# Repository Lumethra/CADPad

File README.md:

# CADPad

## What is this?? 

SHHH, this is a gift, dont spoiler it, SHHHH. But what exactly is this?? Good question. Its a keyboard. Again. Wait, what does again mean, well its my second one. My [Auth75](https://github.com/Lumethra/Auth75) was my first one. Back to what this is. Its technically a keyboard, but I would rather call it a Macropad, because its firmwares purpose is to make 3d modeling in Onshape easier. This is also why its called a CADPad, not Catpad (meow), CADPad. C A D, like CAD-design. 

### Features: 
  - custom 27 keys leyout
      - its kinda ergonomic? kinda.
  - Nice!Nano V2
      - ZMK firmware (hand written, yeeeeee)
      - better ZMK support, because Nice!Nano V2
      - build in BLE support
      - LiPo battery support
      - battery charger + support
  - USB Hub (SL2.1)
      - 1 USB-C upsream
      - 4 USB-C donwstreams
      - USB 2.0 fullspeed

---

## Why though?

This is a gift to [Chroma](https://github.com/Chroma165), my friend who likes to design 3d-models and print them with his 3d-printer. I though it would be nice to gift him a Macropad, my bad, its a CADPad, to make this process easier for him. It was also fun to design a PCB, that has a unique form. 

---

## How?

This CADPads development process was fairly easiy because of the knowledge from Auth75. It has 3 layers of keybinds, which u can cycle through with pressing the 2nd knob. The other knobs keypress is reserved for BLE pairing. 

---

## Renders

| PCB with Components |
| --- |
|  |
|  |

| PCB without Components |
| --- |
|  |
|  |

| Case |
| --- |
|  |

---

## PCB + Schematics

| PCB |
| --- |
|  |

| Schematics |
| --- |
|  |

---

<details>
  <summary>
    <h2>Zine</h2> 
  </summary>

| Zine |
| --- |
|  |

---
</details>

## BOM

| Part | Purpose | Cost | Quantity | Total Cost | LCSC/JLCPC Number | Link |
| --- | --- | --- | --- | --- | --- | --- |
| PCB | connect all of the compoenents | $14.10 | 1 (5) | $14.10 | ~ | [JLCPCB](https://jlcpcb.com/) |
| Nice!Nano V2 | handle the firmware | €24.63 | 1 | €24.63 | ~ | [42keebs](https://42keebs.eu/shop/parts/controllers/nice-nano-v2-wireless-controller/) | 
| Kailh Hotswap Sockets | holding the switches to the PCB without soldering | $0.1183 | 78 | ~$9 | C2803348 | [JLCPCB](https://jlcpcb.com/partdetail/C2803348) |
| Kailh (Cocoa) Switches | the switches you can press | $0 (comes with a Rainy75) | 78 | $0 (already owned) | ~ | ~ |
| Keycaps | goes onto the switches for better look and feel | $0 (3d printing ABS) | 78 | $0 (3d printed) | ~ | ~ |
| EC11 Rotary Encoder Switch | goes uii and click click | $2.22 | 1 | $2.22 | C370970 | [JLCPCB](https://jlcpcb.com/partdetail/C370970) / [Amazon](https://www.amazon.de/-/en/RUNCCI-YUN-Potentiometer-Automotive-Electronics-Multimedia/dp/B09SG3HF9N) |
| USB-C connector | connect to laptop | $0.0740 | 4 | $0.296 | C2765186 | [JLCPCB](https://jlcpcb.com/partdetail/C2765186) |
| SL2.1s | USB Hub core component | $0.2258 | 1 | $0.2258 | C2684433 | [JLCPCB](https://jlcpcb.com/partdetail/C2684433) |
| DW01A | battery protector | $0.0426 | 1 | $0.0426 | C351410 | [JLCPCB](https://jlcpcb.com/partdetail/C351410) |
| FS8205A | mosfet for protector | $0.0470 | 1 | $0.0470 | C2830320 | [JLCPCB](https://jlcpcb.com/partdetail/C2830320) |
| S2B-PH-SM4-TB | LiPo battery connector | $0.2014 | 1 | $0.2014 | C295747 | [JLCPCB](https://jlcpcb.com/partdetail/C295747) |
| Diodes | prevent voltage from backflowing and causing problems | $0.0117 | 82 | ~$0.9594 | C81598 | [JLCPCB](https://jlcpcb.com/partdetail/C81598) |
| Resistors | prevent things go boom | ~$0.0016 | 19 | ~$0.0304 | C23186, C21190, C22775 | [C23186](https://jlcpcb.com/partdetail/C23186) / [C21190](https://jlcpcb.com/partdetail/C21190) / [C22775](https://jlcpcb.com/partdetail/C22775) |
| Capacitors | smooth out the power | $0.0032 - $0.0110 | 14 | ~$0.0956 | C15849, C19666, C14663 | [C15849](https://jlcpcb.com/partdetail/C15849) / [C19666](https://jlcpcb.com/partdetail/C19666) / [C14663](https://jlcpcb.com/partdetail/C14663) |

> the prices can vary depending on the provider <br>
> you can find the JLCPCB parts on [LCSC](https://lcsc.com/) too (exept the PCB and the Pico)

--- 

## Contribute

Want to make anything better? Found any bugs? Anything always going booom?? Feel free to open a PR (pull request) and lets make the project better. ^_^
> the libraries are all imported with [easyeda2kicad](https://github.com/uPesy/easyeda2kicad.py) and [kiswitch](https://github.com/kiswitch/kiswitch)

---

## Thank you

A huge thank you too all these persons helping me making this project possible, thank you helping me sanity check, thank you for all these support. 
> Thank you, <3 u all ^_^

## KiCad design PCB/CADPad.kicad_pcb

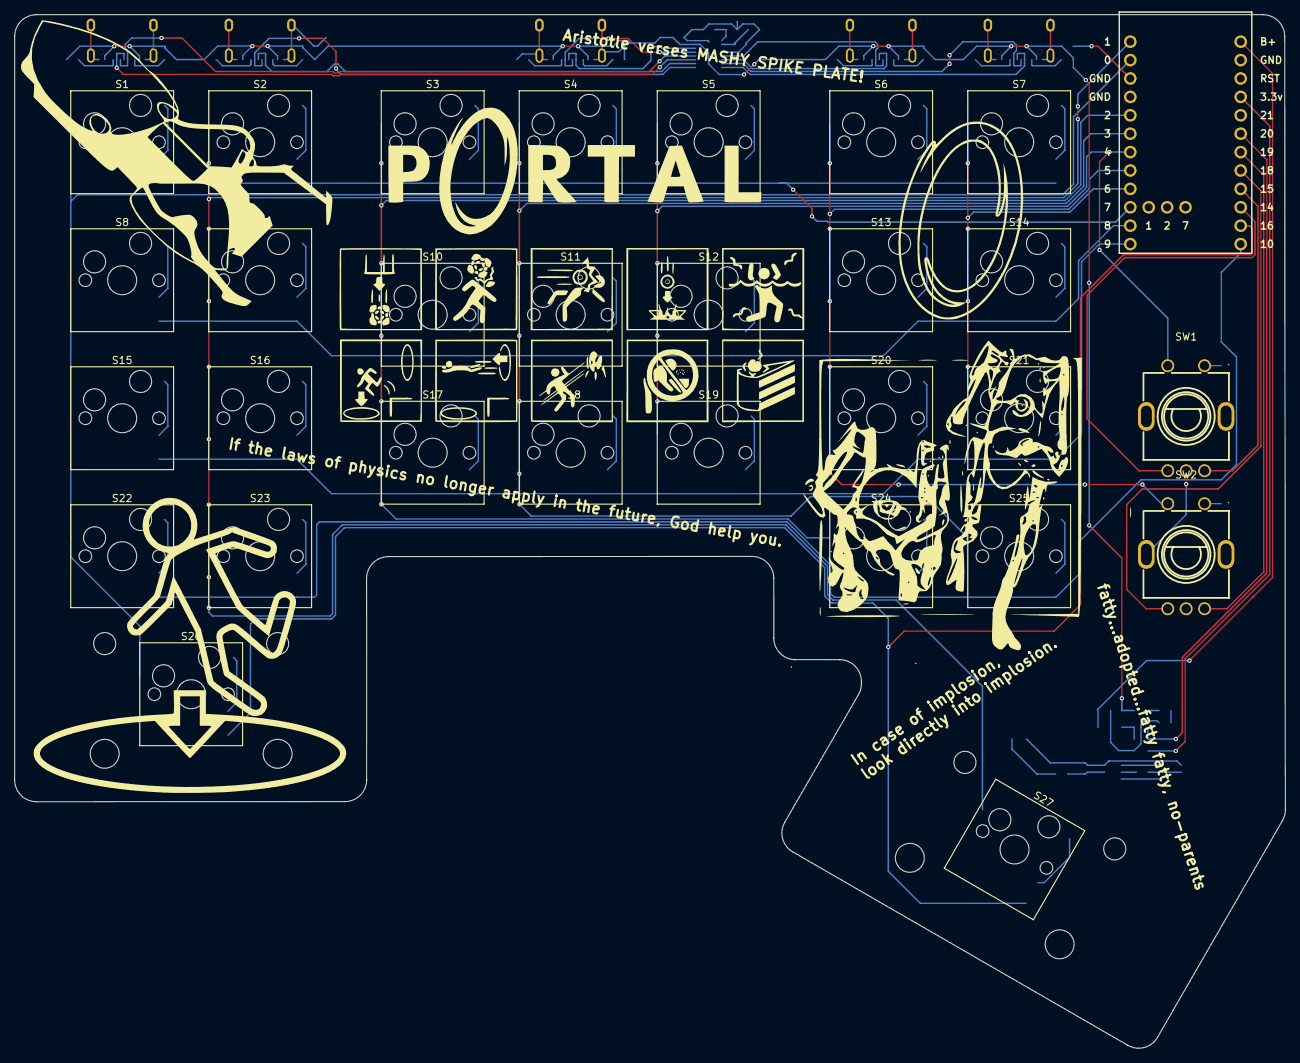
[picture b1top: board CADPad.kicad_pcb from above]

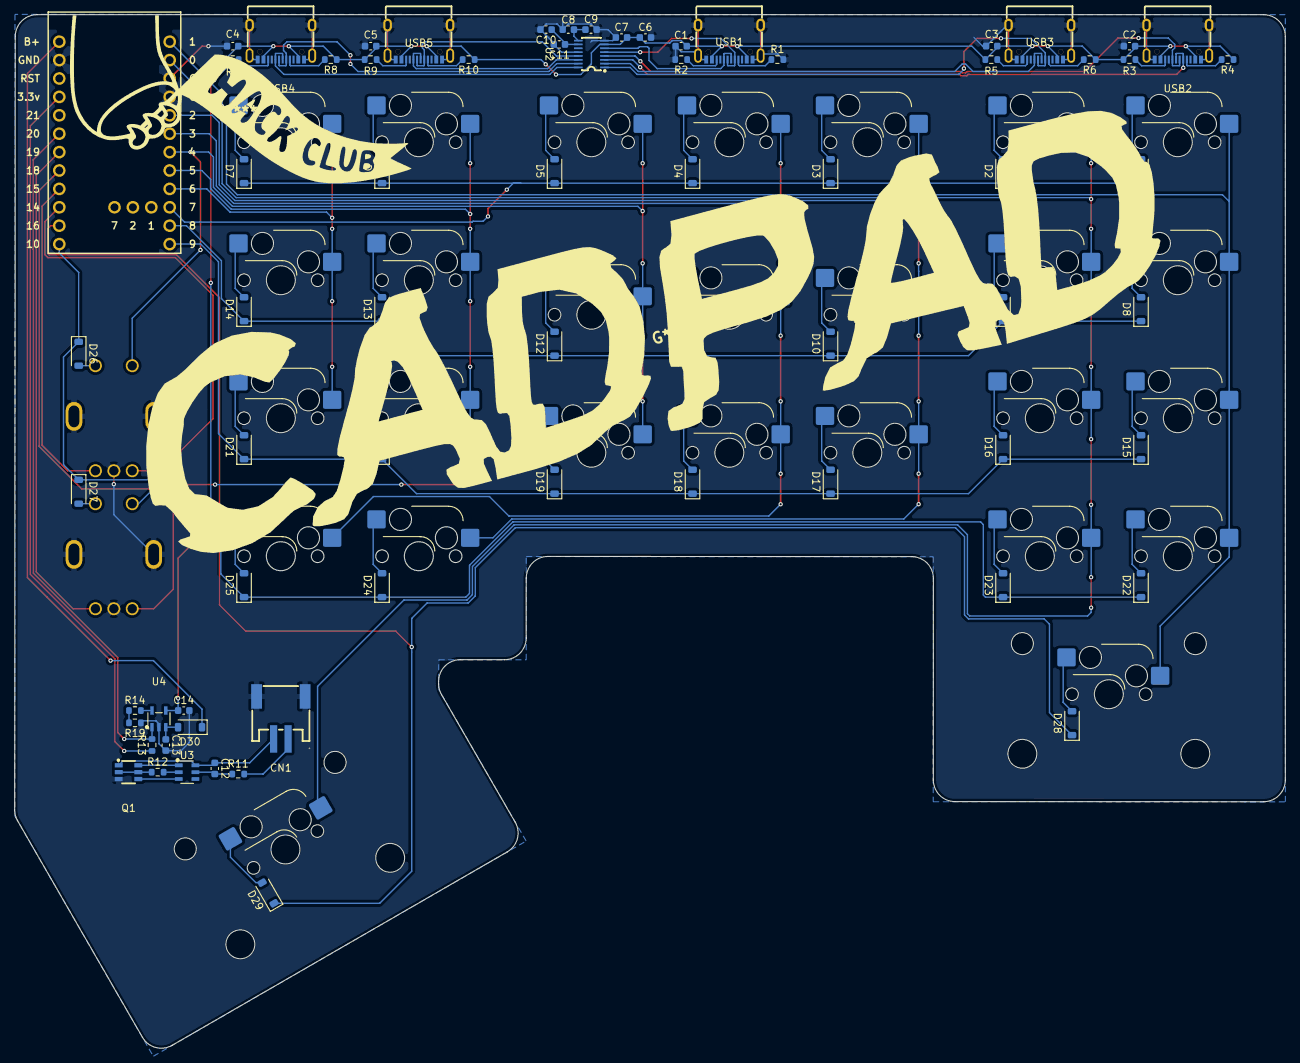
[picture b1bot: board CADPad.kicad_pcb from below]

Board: 2 copper layers, 175.4 x 142.7 mm, 99 parts (69 on the bottom side), 82 nets.

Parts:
C1, C2, C3, C4, C5, C6, C8, C10: 1uf; C_0603_1608Metric
C7, C9, C11, C12: 100nf; C_0603_1608Metric
C13, C14: 4.7uF; C_0603_1608Metric
CN1: S2B-PH-SM4-TB; CONN-SMD_P2.00_S2B-PH-SM4-TB-LF-SN
D1, D2, D3, D4, D5, D6, D7, D8, D9, D10, D11, D12, D13, D14, D15, D16, D17, D18, D19, D20, D21, D22, D23, D24, D25, D26, D27, D28, D29, D30: D_SOD-123
Q1: FS8205A_C2830320; SOT-23-6_L2.9-W1.6-P0.95-LS2.8-BR
R1, R2, R3, R4, R5, R6, R7, R8, R9, R10, R13: 5.1k; R_0603_1608Metric
R11: 100; R_0603_1608Metric
R12, R14, R19: 1k; R_0603_1608Metric
S1, S2, S3, S4, S5, S6, S7, S8, S9, S10, S11, S12, S13, S14, S15, S16, S17, S18, S19, S20, S21, S22, S23, S24, S25, S26, S27: SW_Hotswap_Kailh_MX
SW1, SW2: EC11E15244G1; SW-TH_EC11E15244G1
U1: Nice_Nano_V2
U2: SL2.1S; SSOP-16_L4.6-W2.6-P0.53-LS4.0-BL
U3: DW01A_C351410; SOT-23-6_L2.9-W1.6-P0.95-LS2.8-BL
U4: MCP73831T-2ACI/OT; SOT-23-5_L3.0-W1.7-P0.95-LS2.8-BL
USB1, USB2, USB3, USB4, USB5: TYPE-C 16PIN 2MD; USB-C-SMD_TYPE-C-6PIN-2MD-073

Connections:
+3.3V: R13.1, U1.21 (3.3v)
+5V: C1.1, C2.1, C3.1, C4.1, C5.1, C6.1, C7.1, C14.1, R3.1, R4.1, R5.1, R6.1, R7.1, R8.1, R9.1, R10.1, U2.7 (VDD5), U4.4 (VDD), USB1.2 (VBUS), USB1.11 (VBUS), USB2.2 (VBUS), USB2.11 (VBUS), USB3.2 (VBUS), USB3.11 (VBUS), USB4.2 (VBUS), USB4.11 (VBUS), USB5.2 (VBUS), USB5.11 (VBUS)
/D1/D2: Q1.2 (D1/D2), Q1.5 (D1/D2), R12.1
/DN: U2.5 (UDM), USB1.5 (DN2), USB1.7 (DN1)
/DN1: U2.3 (DM1), USB2.5 (DN2), USB2.7 (DN1)
/DN2: U2.1 (DM2), USB3.5 (DN2), USB3.7 (DN1)
/DN3: U2.15 (DM3), USB4.5 (DN2), USB4.7 (DN1)
/DN4: U2.13 (DM4), USB5.5 (DN2), USB5.7 (DN1)
/DP: U2.6 (UDP), USB1.6 (DP1), USB1.8 (DP2)
/DP1: U2.4 (DP1), USB2.6 (DP1), USB2.8 (DP2)
/DP2: U2.2 (DP2), USB3.6 (DP1), USB3.8 (DP2)
/DP3: U2.16 (DP3), USB4.6 (DP1), USB4.8 (DP2)
/DP4: U2.14 (DP4), USB5.6 (DP1), USB5.8 (DP2)
BATT+: C13.1, D30.2 (A), U4.3 (VBAT)
Batt+: CN1.1, R11.2
Batt-: C12.1, CN1.2, Q1.1 (S1), U3.6 (GND)
Column 1: S1.1, S8.1, S15.1, S22.1, S26.1, U1.2 (0)
Column 2: S2.1, S9.1, S16.1, S23.1, S27.1, U1.1
Column 3: S3.1, S10.1, S17.1, S24.1, U1.5 (2)
Column 4: S4.1, S11.1, S18.1, S25.1, U1.6 (3)
Column 5: S5.1, S12.1, S19.1, SW1.D, U1.7 (4)
Column 6: S6.1, S13.1, S20.1, SW2.D, U1.8 (5)
Column 7: S7.1, S14.1, S21.1, U1.9 (6)
GND: C1.2, C2.2, C3.2, C4.2, C5.2, C6.2, C7.2, C8.2, C9.2, C10.2, C11.2, C13.2, C14.2, CN1.3, CN1.4, Q1.3 (S2), R1.2, R2.2, R19.1, SW1.6, SW1.7, SW1.C, SW2.6, SW2.7, SW2.C, U1.3 (GND), U1.4 (GND), U1.23 (GND), U2.8 (VSS), U2.12 (XIN), U4.2 (VSS), USB1.1 (GND), USB1.12 (GND), USB1.13 (SHELL), USB1.14 (SHELL), USB2.1 (GND), USB2.12 (GND), USB2.13 (SHELL), USB2.14 (SHELL), USB3.1 (GND), USB3.12 (GND), USB3.13 (SHELL), USB3.14 (SHELL), USB4.1 (GND), USB4.12 (GND), USB4.13 (SHELL), USB4.14 (SHELL), USB5.1 (GND), USB5.12 (GND), USB5.13 (SHELL), USB5.14 (SHELL)
Knob_1 A: SW1.A, U1.15 (14)
Knob_1 B: SW1.B, U1.16 (15)
Knob_1 S_Out: D26.2 (A), SW1.E
Knob_2 A: SW2.A, U1.17 (18)
Knob_2 B: SW2.B, U1.18 (19)
Knob_2 S_Out: D27.2 (A), SW2.E
unnamed: D1.2 (A), S1.2
unnamed: D2.2 (A), S2.2
unnamed: D3.2 (A), S3.2
unnamed: D4.2 (A), S4.2
unnamed: D5.2 (A), S5.2
unnamed: D6.2 (A), S6.2
unnamed: D7.2 (A), S7.2
unnamed: D8.2 (A), S8.2
unnamed: D9.2 (A), S9.2
unnamed: D10.2 (A), S10.2
unnamed: D11.2 (A), S11.2
unnamed: D12.2 (A), S12.2
unnamed: D13.2 (A), S13.2
unnamed: D14.2 (A), S14.2
unnamed: D15.2 (A), S15.2
unnamed: D16.2 (A), S16.2
unnamed: D17.2 (A), S17.2
unnamed: D18.2 (A), S18.2
unnamed: D19.2 (A), S19.2
unnamed: D20.2 (A), S20.2
unnamed: D21.2 (A), S21.2
unnamed: D22.2 (A), S22.2
unnamed: D23.2 (A), S23.2
unnamed: D24.2 (A), S24.2
unnamed: D25.2 (A), S25.2
unnamed: D28.2 (A), S26.2
unnamed: D29.2 (A), S27.2
unnamed: D30.1 (K), U1.24 (B+)
unnamed: Q1.6 (G1), U3.1 (OD)
unnamed: Q1.4 (G2), U3.3 (OC)
unnamed: R14.1, R19.2
unnamed: C10.1, C11.1, U2.10 (VDD18)
unnamed: C8.1, C9.1, U2.9 (VDD33)
unnamed: C12.2, R11.1, U3.5 (VCC)
unnamed: R12.2, U3.2 (VM)
unnamed: R14.2, U4.5 (PROG)
unnamed: R1.1, USB1.4 (CC1)
unnamed: R2.1, USB1.10 (CC2)
unnamed: R4.2, USB2.4 (CC1)
unnamed: R3.2, USB2.10 (CC2)
unnamed: R6.2, USB3.4 (CC1)
unnamed: R5.2, USB3.10 (CC2)
unnamed: R8.2, USB4.4 (CC1)
unnamed: R7.2, USB4.10 (CC2)
unnamed: R10.2, USB5.4 (CC1)
unnamed: R9.2, USB5.10 (CC2)
Row 1: D1.1 (K), D2.1 (K), D3.1 (K), D4.1 (K), D5.1 (K), D6.1 (K), D7.1 (K), U1.10 (7)
Row 2: D8.1 (K), D9.1 (K), D10.1 (K), D11.1 (K), D12.1 (K), D13.1 (K), D14.1 (K), U1.11 (8)
Row 3: D15.1 (K), D16.1 (K), D17.1 (K), D18.1 (K), D19.1 (K), D20.1 (K), D21.1 (K), U1.12 (9)
Row 4: D22.1 (K), D23.1 (K), D24.1 (K), D25.1 (K), D26.1 (K), D27.1 (K), U1.13 (10)
Row 5: D28.1 (K), D29.1 (K), U1.14 (16)
STAT: R13.2, U1.19 (20), U4.1 (STAT)

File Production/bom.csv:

Name,Designator,Footprint,Quantity,Value,Price,LCSC Part #,Purchase Link
Capacitors 1uF,"C1, C10, C2, C3, C4, C5, C6, C8",0603,8,1uF,$0.0032,C15849,https://jlcpcb.com/partdetail/C15849
Capacitors 100nF,"C11, C12, C7, C9",0603,4,100nF,$0.0032,C14663,https://jlcpcb.com/partdetail/C14663
Capacitors 4.7uF,"C13, C14",0603,2,4.7uF,$0.0110,C19666,https://jlcpcb.com/partdetail/C19666
S2B-PH-SM4-TB,CN1,CONN-SMD_P2.00_S2B-PH-SM4-TB-LF-SN,1,S2B-PH-SM4-TB,$0.2014,C295747,https://jlcpcb.com/partdetail/C295747
Diodes,"D1, D10, D11, D12, D13, D14, D15, D16, D17, D18, D19, D2, D20, D21, D22, D23, D24, D25, D26, D27, D28, D29, D3, D30, D4, D5, D6, D7, D8, D9",D_SOD-123,30,~,$0.0117,C81598,https://jlcpcb.com/partdetail/C81598
FS8205A,Q1,SOT-23-6_L2.9-W1.6-P0.95-LS2.8-BR,1,FS8205A_C2830320,$0.0470,C2830320,https://jlcpcb.com/partdetail/C2830320
Resistors 5.1k,"R1, R10, R13, R2, R3, R4, R5, R6, R7, R8, R9",0603,11,5.1k,$0.0016,C23186,https://jlcpcb.com/partdetail/C23186
Resistors 100,R11,0603,1,100,$0.0016,C22775,https://jlcpcb.com/partdetail/C22775
Resistors 1k,"R12, R14, R19",0603,3,1k,$0.0016,C21190,https://jlcpcb.com/partdetail/C21190
Kailh Hotswap Sockets,"S1, S10, S11, S12, S13, S14, S15, S16, S17, S18, S19, S2, S20, S21, S22, S23, S24, S25, S26, S27, S3, S4, S5, S6, S7, S8, S9",SW_Hotswap_Kailh_MX,27,~,$0.1183,C2803348,https://jlcpcb.com/partdetail/C2803348
Nice Nano V2,U1,Nice_Nano_V2,1,Nice_Nano_V2,€24.63,~,https://42keebs.eu/shop/parts/controllers/nice-nano-v2-wirel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
SL2.1S,U2,SSOP-16_L4.6-W2.6-P0.53-LS4.0-BL,1,SL2.1S,$0.2258,C2684433,https://jlcpcb.com/partdetail/C2684433
DW01A,U3,SOT-23-6_L2.9-W1.6-P0.95-LS2.8-BL,1,DW01A_C351410,$0.0426,C351410,https://jlcpcb.com/partdetail/C351410
MCP73831T-2ACI/OT,U4,SOT-23-5_L3.0-W1.7-P0.95-LS2.8-BL,1,MCP73831T-2ACI/OT,$0.7585,C424093,https://jlcpcb.com/partdetail/C424093
USB-C Connector,"USB1, USB2, USB3, USB4, USB5",USB-C-SMD_TYPE-C-6PIN-2MD-073,5,TYPE-C 16PIN 2MD,$0.0740,C2765186,https://jlcpcb.com/partdetail/C2765186

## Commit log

2026-05-22 Create Project
2026-05-29 adding firmware (note: its a seperate repo)
2026-05-29 assigning LSCS numbers and regenerating PCB-CAD
2026-05-29 enhance BOM
2026-05-29 enhance again (minor)
2026-05-30 Giving the readme a basic structure
2026-05-30 add images
2026-05-30 finishing README (almost, maybe, might be)
2026-05-30 last save before zine
2026-05-30 zine
2026-05-30 case
2026-05-30 case 3d render
2026-05-30 adding Case
2026-05-30 zine as pdf
